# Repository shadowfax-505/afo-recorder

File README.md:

# AFO Research Recorder

An engineering research platform for synchronized lower-limb EMG and motion acquisition. The recorder samples two MyoWare 2.0 RAW channels by default, supports foot and shank IMUs, stores the primary recording on microSD, and sends a best-effort live copy over ESP32-S3 Wi-Fi.

[Open the live project](https://shadowfax-505.github.io/afo-recorder/) · [Read the documentation](https://shadowfax-505.github.io/afo-recorder/documentation/) · [Download complete packages](https://github.com/shadowfax-505/afo-recorder/releases/tag/v0.1.6)

> **Engineering status:** the firmware, file format, host tools, PCB rules, wiring data, simulations, and browser viewers have automated evidence. No recorder has yet passed the physical bench sequence. This repository does not claim measured signal quality, runtime, wearable safety, or clinical performance.

## What is included

| Layer | Included | Current evidence |
|---|---|---|
| Acquisition | ESP32-S3 firmware for AD7606 or ADS131M04 and two IMU families | Released profiles compile; hardware timing remains unmeasured |
| Storage | Versioned binary records, counters, metadata, CRC, and interrupted-file recovery | Converter and fault-injection tests pass |
| Live view | Best-effort Wi-Fi receiver for a laptop | Loopback/software checks only |
| Hardware | Breadboard plans, compact PCB projects, manufacturing exports, and 3D viewers | ERC/DRC and consistency checks pass; fabrication review remains open |
| Lab workflow | Ten gated stages from power rails to MyoWare integration | Procedures and result sheets supplied; measured results are blank |

## Choose a configuration

All packages target 8 kHz per enabled EMG channel and 200 Hz from each foot/shank IMU.

| ADC | EMG capacity | Motion sensor | Package |
|---|---:|---|---|
| AD7606, 16-bit simultaneous | Fixed 2 | ICM-42688-P | `ad7606-two-channel-icm42688` |
| AD7606, 16-bit simultaneous | Fixed 2 | GY-521 / MPU-6050 | `ad7606-two-channel-mpu6050` |
| AD7606, 16-bit simultaneous | 2 or 4 | ICM-42688-P | `ad7606-expandable-icm42688` |
| AD7606, 16-bit simultaneous | 2 or 4 | GY-521 / MPU-6050 | `ad7606-expandable-mpu6050` |
| ADS131M04, 24-bit simultaneous | 2 or 4 | ICM-42688-P | `ads131m04-expandable-icm42688` |
| ADS131M04, 24-bit simultaneous | 2 or 4 | GY-521 / MPU-6050 | `ads131m04-expandable-mpu6050` |

Use one package end to end. Do not combine an ICM wiring plan with MPU firmware or a breadboard binary with the compact-PCB SD pin assignment. The fixed-two packages intentionally reject four-channel builds.

### Arduino Mega bench setup

A separate, simpler setup lives in [`designs/mega-myoware-shield-mpu6050`](designs/mega-myoware-shield-mpu6050/README.md): an Arduino Mega 2560 with the MyoWare 2.0 Arduino Shield, up to two MPU-6050 IMUs and a ZS-040 Bluetooth module, plus a browser app for live readings and saved recordings. It uses the Mega's 10-bit ADC at up to a few hundred samples per second, so it is not a substitute for the six packages above.

## Start here

1. Read the [project manual](documentation/README.md) and choose one package.
2. Open that package's `viewer/build.html` and begin at Stage 1.
3. Qualify each module before attaching it to the controller.
4. Use synthetic signals with no person attached for every instrument-connected test.
5. Record actual measurements and pass every stage before ordering the compact PCB.

For a local copy of the website:

```sh
python3 -m http.server 8769
```

Then open <http://127.0.0.1:8769/>. The 3D viewers require HTTP and do not work correctly from a `file://` URL.

## Repository map

```text
designs/<configuration>/
├── breadboard/      terminal-level plans, placements, and wire tables
├── firmware/        ESP-IDF source and build profiles
├── hardware/        KiCad source and module references
├── host/            converter, live receiver, plots, and tests
├── manufacturing/   Gerber, drill, BOM, placement, and STEP exports
├── simulations/     analog and acquisition fault models
├── docs/            package-specific build and validation records
└── viewer/          guided build, 3D assembly, and PCB preview

documentation/       project-wide manual, status, and evidence summaries
validation/          blank or user-entered bench-session records
design-catalog.json  machine-readable list of all six configurations
```

## Validation language

The focused **AD7606 / fixed two-channel / ICM-42688-P** build has a [current integrated verification report](designs/ad7606-two-channel-icm42688/docs/integrated-verification.md). Its laboratory firmware is now **ad7606-2ch-1.12**, and **all 18 integrated Wokwi cases pass on its simulation image** (12 October 2026; the 1.11 run exposed a Wi-Fi preview race that 1.12 fixes) (32/30 µs ICM-42688 timestamp ticks, 2.44 s PSRAM record queue, per-device Wi-Fi password, IMU-only bench verdicts at the datasheet’s ±2 % clock tolerance, fitted IMU host time); its [ICM-42688-P setup](designs/ad7606-two-channel-icm42688/docs/icm-module.md) was checked against the official TDK datasheet (DS-000347 rev 1.6) and a register-level sensor model, and its AD7606 against ADI’s Rev. G data sheet. Following ADI AN-1091, the PCB now holds the ADC in shutdown until the firmware releases STBY on GPIO14, and a BAT760 diode limits VDRIVE − AVCC during power-up (DRC/ERC clean; not yet built). It compiles and passes the host and native tests but has not been rerun in Wokwi. All 18 v1.6 cases pass actual ESP-IDF execution in Wokwi’s web simulator, with real FreeRTOS/FatFS/lwIP and documented sensor, storage and radio substitutes. Nominal saved acquisition has no detected sample loss; current laptop socket/API/browser/archive checks correctly retain preview and packet gaps. Local coverage includes a 60-second, 480,000-frame production-driver pipeline. The unqualified QEMU timing experiment and historical incomplete CLI runs remain visible. Physical performance remains unmeasured; On 12 October 2026 the three other AD7606 designs received the same STBY/supply-ramp PCB fix and firmware (dual-1.4 / mpu6050-1.4); the ADS131M04 designs need none. On 12 October 2026 the other five designs also received the 1.12 Wi-Fi preview fix (each live session's metadata is sent before its first data packet) and were rebuilt as dual-1.5 / mpu6050-1.5; they were not rerun in Wokwi. On 11 October 2026 the other five designs received the shared firmware fixes (PSRAM record queue, per-device Wi-Fi password, metadata limit; 32/30 µs ticks for the ICM designs) and the fixed-two recorder corrections (worker lifecycle, fault latching, AD7606 BUSY confirmation, windowed diagnostics) and were rebuilt (firmware dual-1.3 / mpu6050-1.3); their other evidence is unchanged.

- **Verified in software** means a check, build, simulation, or test has a saved result in this repository.
- **Simulated** means generated inputs exercised a model or data path; it is not a hardware measurement.
- **Pending hardware** means the result must be measured on the assembled module, breadboard, or PCB.
- **Passed — measured** should be entered only by the person who performed the lab procedure and retained the evidence.

The latest project-level evidence reports six host suites with 242 tests, 26 compiled recording profiles, clean ERC/DRC reports for all six variants, and complete named wiring inventories. The same evidence explicitly marks physical validation as pending.

## Safety and research use

Disconnect charging cables, USB, and mains-connected instruments while electrodes are attached. Early electrical tests use synthetic sources with no person attached. Human recordings require appropriate institutional approval, informed consent, and an electrical-safety review. This system is a research recorder, not a medical device or an AFO controller.

## Documentation and attribution

- [Project manual and reading order](documentation/README.md)
- [System architecture](documentation/system-architecture.md)
- [Staged lab build](documentation/lab-build-guide.md)
- [Recording and analysis](documentation/recording-and-analysis.md)
- [Validation status](documentation/validation-status.md)
- [Manufacturer evidence](documentation/manufacturer-evidence.md)
- [Third-party notices](THIRD_PARTY_NOTICES.md)

Project lead: **Muttakin Rahman**. Manufacturer credits, source references, and third-party licence notices are retained. Publication does not change the ownership of external boards, CAD, datasheets, libraries, or photographs.

Open the [complete-system guide](designs/ad7606-two-channel-icm42688/docs/whole-system.md) for the physical assembly, saved Wokwi scene and downloadable simulation bundle.

The latest focused checks include a [complete-scene digital timing capture](designs/ad7606-two-channel-icm42688/docs/digital-timing.md) and a [saved-data interpretation guide](designs/ad7606-two-channel-icm42688/docs/data-interpretation.md). The independent audit checks 21,116 original record CRCs and CSV rows across two synthetic captures. Downloadable examples include binary recordings, metadata, quality reports and readable analysis tables; original measurement bytes are preserved. Physical storage, signal accuracy and timing calibration remain pending.

## Active build: sequential development

The [AD7606 two-channel / ICM-42688-P workbook](designs/ad7606-two-channel-icm42688/development/README.md) organizes assembly, exact new wires, measurements and evidence review one module at a time. Read the [personal system explanation](designs/ad7606-two-channel-icm42688/docs/understanding-the-recorder.md) for the AFO and neuromuscular research rationale. The other five configurations remain unchanged.

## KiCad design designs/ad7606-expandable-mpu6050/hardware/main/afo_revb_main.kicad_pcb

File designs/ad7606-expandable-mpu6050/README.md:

# Project lead: Muttakin Rahman

Start with [the guided build](viewer/build.html). The [source and licence notices](THIRD_PARTY_NOTICES.md) distinguish project material from third-party assets.

> Current assembly entrypoint: [complete build guide](docs/build-guide.html), [module qualification](docs/module-qualification.md), and [current validation](docs/validation-report.md). Historical reports and stage overview drawings are retained for traceability.

# AD7606 · Two or four EMG channels — MPU-6050

**12 October 2026 firmware update (`mpu6050-1.5`):** the Wi-Fi live task now announces a new session (its metadata packet) before that session's first data packet. Earlier firmware could send a record dequeued just after the per-loop metadata check first, and the laptop receiver dropped it as an unknown session. `firmware/main/wifi_live.c` is now byte-identical to the fixed two-channel AD7606 / ICM design's `ad7606-2ch-1.12`, where the fix was found by and passes the 18-case Wokwi matrix; this package was not rerun in Wokwi. All profiles were rebuilt with ESP-IDF v5.4.2 and host tests pass; cross-compiled only, not flashed or simulated.

**12 October 2026 PCB and firmware update (`mpu6050-1.4`):** the AD7606 supply rail is made from 3V3D by a charge pump, so VDRIVE rises before AVCC at every power-up. Following ADI application note AN-1091, AD7606 STBY (pin 7) is now driven by ESP32 GPIO14 with a 100 kΩ pull-down (R70), so the converter stays in full shutdown until the firmware releases it, waits 30 ms and resets it. A BAT760 Schottky (D30) from 3V3D to 5V_ADC limits VDRIVE − AVCC while the pump starts. The pin-8 (RANGE) ground tie that blocked pin 7 was re-routed to its own ground via. KiCad DRC (0 violations, 0 unconnected) and ERC (0) are clean, the package validator passes, and manufacturing files were re-exported; the board has not been built. Breadboard builds do not drive GPIO14. The same change, with its datasheet analysis, is described in the fixed two-channel ICM design's [circuit review](../ad7606-two-channel-icm42688/docs/circuit-audit.html).

**11 October 2026 firmware update (`mpu6050-1.3`):** the SD record queue now holds 20,480 records (about 2.44 s) in PSRAM instead of 2,048 (0.244 s), which was shorter than the 250–500 ms write-busy time an SD card may legally take; no Wi-Fi password is compiled in: each recorder generates a random 16-character password on first boot, stores it in NVS and prints it on the USB console at every boot (`Laptop AP: AFO-Recorder-B; password: …`); read it once at the bench and keep it private; the live-metadata limit is 1,800 bytes: this package's session metadata (about 1,360–1,430 bytes) exceeded the previous 1,280-byte limit, so earlier firmware silently disabled the Wi-Fi preview. All profiles were rebuilt with ESP-IDF v5.4.2 and are cross-compiled only, not flashed or simulated. Firmware `mpu6050-1.3` (same day) also ports the corrections from the fixed-two AD7606/ICM recorder: the AD7606 driver confirms BUSY after every CONVST, waits for BUSY to fall within an 80 µs deadline, and stops rather than reading a stale or overlapping conversion; recording tasks are suspended and then joined and deleted by the recorder, so an early fault cannot free a task the recorder still uses; any fault stops acquisition; both IMU stop calls are attempted; queued data is synced before the END record, and the Wi-Fi stop verdict is sent only after the final write, sync and close checks; diagnostics acquire in one-second windows and stop triggers while printing; the IMU waits up to 100 ms for its first interrupt. The fixed-two native recorder harness (19 fault and lifecycle cases) passes for every profile of this package under ASan/UBSan.

[Open the assembly viewer](viewer/index.html) · [Build guide](docs/staged-build-guide.md) · [Wiring guide](docs/breadboard-assembly.md)

[MPU wiring, timing and limits](docs/mpu6050-wiring-and-timing.md) · [Validation report](docs/validation-report.md)

Serve this folder over HTTP; opening the viewer directly as a local HTML file will block asset fetches in most browsers. Standard filenames such as CMakeLists.txt, main.c, index.html and KiCad project members are retained for tool compatibility.

All hardware remains an engineering prototype pending physical validation. Module pin positions and outstanding wiring gates are documented; no board order is implied.

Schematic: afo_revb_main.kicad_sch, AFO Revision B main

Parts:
C1, C10, C32, C33, C34, C43, C44, C200, C201, C202, C204: 100nF; C_0603_1608Metric; MPN GRM188R71C104KA01D
C2, C203, C207, C208: 10uF; C_0805_2012Metric; MPN GRM21BR61A106KE19L
C3, C30, C31, C45, C46, C205, C206, C212: 1uF; C_0603_1608Metric; MPN GRM188R61A105KA61D
C11, C40, C41, C42: 22uF; C_0805_2012Metric; MPN GRM21BR61A226ME44L
C12: 10nF; C_0603_1608Metric; MPN GRM188R71H103KA01D
C100, C101, C110, C111, C120, C121, C130, C131: 47nF; C_0603_1608Metric; MPN GRM188R71H473KA61D
C102, C112, C122, C132: 1nF; C_0603_1608Metric; MPN GRM1885C1H102JA01D
C210, C211: 2.2uF; C_0603_1608Metric; MPN GRM188R61A225KE15D
D1: USB ESD; SOT-23-6; MPN USBLC6-2SC6
D10, D11, D12, D13: BAV199; SOT-23; MPN BAV199,215
D20: green; LED_0603_1608Metric; MPN LTST-C190KGKT
D21: red; LED_0603_1608Metric; MPN LTST-C190KRKT
D22: amber; LED_0603_1608Metric; MPN LTST-C190KSKT
D30: BAT760; D_SOD-323; MPN BAT760,115
H1, H2, H3: M2 mounting; MountingHole_2.2mm_M2; MPN MECHANICAL
J1: USB-C (battery powered); USB_C_Receptacle_GCT_USB4105-xx-A_16P_TopMnt_Horizontal; MPN USB4105-GF-A
J2: microSD; microSD_HC_Hirose_DM3AT-SF-PEJM5; MPN DM3AT-SF-PEJM5
J3: FOOT MPU6050; JST_GH_BM08B-GHS-TBT_1x08-1MP_P1.25mm_Vertical; MPN BM08B-GHS-TBT(LF)(SN)
J4: SHANK MPU6050; JST_GH_BM08B-GHS-TBT_1x08-1MP_P1.25mm_Vertical; MPN BM08B-GHS-TBT(LF)(SN)
J5: EMG1; JST_GH_BM03B-GHS-TBT_1x03-1MP_P1.25mm_Vertical; MPN BM03B-GHS-TBT(LF)(SN)
J6: EMG2; JST_GH_BM03B-GHS-TBT_1x03-1MP_P1.25mm_Vertical; MPN BM03B-GHS-TBT(LF)(SN)
J7: EMG3; JST_GH_BM03B-GHS-TBT_1x03-1MP_P1.25mm_Vertical; MPN BM03B-GHS-TBT(LF)(SN)
J8: EMG4; JST_GH_BM03B-GHS-TBT_1x03-1MP_P1.25mm_Vertical; MPN BM03B-GHS-TBT(LF)(SN)
J9: PROTECTED 1S BATTERY; JST_GH_BM02B-GHS-TBT_1x02-1MP_P1.25mm_Vertical; MPN BM02B-GHS-TBT(LF)(SN)
J10: Expansion; JST_GH_BM06B-GHS-TBT_1x06-1MP_P1.25mm_Vertical; MPN BM06B-GHS-TBT(LF)(SN)
L1: 1.5uH; L_Coilcraft_XAL4020-XXX; MPN XAL4020-152MEC
Q1: DMP2035U; SOT-23; MPN DMP2035U-7
Q2: 2N7002; SOT-23; MPN 2N7002,215
R1, R2, R3, R10, R11, R12, R13, R14, R26, R30, R31, R33, R40, R41: 10k; R_0603_1608Metric; MPN RC0603FR-0710KL
R15, R22, R23: 33; R_0603_1608Metric; MPN RC0603FR-0733RL
R20, R21: 5.1k; R_0603_1608Metric; MPN RC0603FR-075K1L
R24, R51, R52, R53, R54, R70: 100k; R_0603_1608Metric; MPN RC0603FR-07100KL
R25, R101, R111, R121, R131: 1M; R_0603_1608Metric; MPN RC0603FR-071ML
R42, R104, R114, R124, R134: 100; R_0603_1608Metric; MPN RC0603FR-07100RL
R50: 316k; R_0603_1608Metric; MPN RC0603FR-07316KL
R60, R61, R62: 1k; R_0603_1608Metric; MPN RC0603FR-071KL
R100, R102, R110, R112, R120, R122, R130, R132: 3.3k; R_0603_1608Metric; MPN RC0603FR-073K3L
SW1: POWER; SW_SPDT_CK_JS102011SAQN; MPN JS102011SAQN
SW2: BOOT; SW_SPST_TL3342; MPN TL3342F160QG
SW3: EN; SW_SPST_TL3342; MPN TL3342F160QG
SW4: BUTTON; SW_SPST_TL3342; MPN TL3342F160QG
U1: ESP32-S3-WROOM-1-N8R8; ESP32-S3-WROOM-1; MPN ESP32-S3-WROOM-1-N8R8
U2: AD7606BSTZ; LQFP-64_10x10mm_P0.5mm; MPN AD7606BSTZ
U3, U4: MCP6004T-I/ST; TSSOP-14_4.4x5mm_P0.65mm; MPN MCP6004T-I/ST
U5: MCP6001T-I/OT; SOT-23-5; MPN MCP6001T-I/OT
U6: TPS63070RNMR; TI_RNM0015A; MPN TPS63070RNMR
U7: TPS7A2030PDBVR; SOT-23-5; MPN TPS7A2030PDBVR
U8: TPS60150DRVR; TPS60150_DRV0006D; MPN TPS60150DRVR

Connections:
3V0A: C32.1 (3V0A), C33.1 (3V0A), C34.1 (3V0A), C46.1 (3V0A), D10.2 (3V0A), D11.2 (3V0A), D12.2 (3V0A), D13.2 (3V0A), J5.1 (3V0A), J6.1 (3V0A), J7.1 (3V0A), J8.1 (3V0A), R40.1 (3V0A), U3.4 (3V0A), U4.4 (3V0A), U5.5 (3V0A), U7.5 (3V0A)
3V3D: C1.1 (3V3D), C2.1 (3V3D), C10.1 (3V3D), C11.1 (3V3D), C41.1 (3V3D), C42.1 (3V3D), C45.1 (3V3D), C204.1 (3V3D), C210.1 (3V3D), D30.2 (A), J2.4 (3V3D), J3.1 (3V3D), J4.1 (3V3D), J10.1 (3V3D), R1.1 (3V3D), R2.1 (3V3D), R3.1 (3V3D), R10.1 (3V3D), R11.1 (3V3D), R12.1 (3V3D), R13.1 (3V3D), R14.1 (3V3D), R26.1 (3V3D), R30.1 (3V3D), R31.1 (3V3D), R33.1 (3V3D), R50.1 (3V3D), R52.1 (3V3D), U1.2 (3V3), U2.6 (PAR_SER), U2.23 (VDRIVE), U2.34 (REF_SELECT), U6.7 (3V3D), U6.8 (3V3D), U7.1 (3V3D), U7.3 (3V3D), U8.2 (3V3D), U8.6 (3V3D)
5V_ADC: C200.1 (5V_ADC), C201.1 (5V_ADC), C202.1 (5V_ADC), C203.1 (5V_ADC), C211.1 (5V_ADC), D30.1 (K), U2.1 (AVCC), U2.37 (5V_ADC), U2.38 (5V_ADC), U2.48 (5V_ADC), U8.3 (5V_ADC)
ADC_CONVST: U1.19 (GPIO11), U2.9 (CONVST_A), U2.10 (CONVST_B)
ADC_CS: R33.2 (ADC_CS), U1.18 (GPIO10), U2.13 (CS_N)
ADC_DRDY: U1.12 (GPIO8), U2.14 (BUSY)
ADC_MISO: U1.21 (GPIO13), U2.24 (DOUTA)
ADC_REF: C207.1 (ADC_REF), U2.42 (REFIN_OUT)
ADC_REFCAP: C208.1 (ADC_REFCAP), U2.44 (REFCAP_A), U2.45 (REFCAP_B)
ADC_RESET: U1.17 (GPIO9), U2.11 (RESET)
ADC_SCK: U1.20 (GPIO12), U2.12 (SCLK)
ADC_STBY: R70.1 (ADC_STBY), U1.22 (GPIO14), U2.7 (STBY_N)
AIN0P: C102.1 (AIN0P), R104.2 (AIN0P), U2.49 (AIN0P)
AIN1P: C112.1 (AIN1P), R114.2 (AIN1P), U2.51 (AIN1P)
AIN2P: C122.1 (AIN2P), R124.2 (AIN2P), U2.53 (AIN2P)
AIN3P: C132.1 (AIN3P), R134.2 (AIN3P), U2.55 (AIN3P)
BAT_SENSE: C44.1 (BAT_SENSE), R53.2 (BAT_SENSE), R54.1 (BAT_SENSE), U1.39 (GPIO1)
BOOT: R2.2 (BOOT), SW2.1 (BOOT), U1.27 (GPIO0)
BUF0A: R102.1 (BUF0A), U3.1 (BUF0A), U3.2 (BUF0A)
BUF0B: R104.1 (BUF0B), U4.1 (BUF0B), U4.2 (BUF0B)
BUF1A: R112.1 (BUF1A), U3.6 (BUF1A), U3.7 (BUF1A)
BUF1B: R114.1 (BUF1B), U4.6 (BUF1B), U4.7 (BUF1B)
BUF2A: R122.1 (BUF2A), U3.8 (BUF2A), U3.9 (BUF2A)
BUF2B: R124.1 (BUF2B), U4.8 (BUF2B), U4.9 (BUF2B)
BUF3A: R132.1 (BUF3A), U3.13 (BUF3A), U3.14 (BUF3A)
BUF3B: R134.1 (BUF3B), U4.13 (BUF3B), U4.14 (BUF3B)
BUTTON: R3.2 (BUTTON), SW4.1 (BUTTON), U1.11 (GPIO18)
CP_MINUS: C212.2 (CP_MINUS), U8.5 (CP_MINUS)
CP_PLUS: C212.1 (CP_PLUS), U8.4 (CP_PLUS)
EN: C3.1 (EN), R1.2 (EN), SW3.1 (EN), U1.3 (EN)
EXP_SCL: J10.4 (EXP_SCL), U1.25 (GPIO48)
EXP_SDA: J10.3 (EXP_SDA), U1.24 (GPIO47)
FB: R50.2 (FB), R51.1 (FB), U6.5 (FB)
FOOT_AD0: J3.6 (FOOT_AD0), R30.2 (FOOT_AD0), U1.7 (GPIO7)
FOOT_INT: J3.7 (FOOT_INT), U1.9 (GPIO16)
GND: C1.2 (GND), C2.2 (GND), C3.2 (GND), C10.2 (GND), C11.2 (GND), C12.2 (GND), C30.2 (GND), C31.2 (GND), C32.2 (GND), C33.2 (GND), C34.2 (GND), C40.2 (GND), C41.2 (GND), C42.2 (GND), C43.2 (GND), C44.2 (GND), C45.2 (GND), C46.2 (GND), C100.2 (GND), C101.2 (GND), C102.2 (GND), C110.2 (GND), C111.2 (GND), C112.2 (GND), C120.2 (GND), C121.2 (GND), C122.2 (GND), C130.2 (GND), C131.2 (GND), C132.2 (GND), C200.2 (GND), C201.2 (GND), C202.2 (GND), C203.2 (GND), C204.2 (GND), C205.2 (GND), C206.2 (GND), C207.2 (GND), C208.2 (GND), C210.2 (GND), C211.2 (GND), D1.2 (GND), D10.1 (GND), D11.1 (GND), D12.1 (GND), D13.1 (GND), D20.1 (GND), D21.1 (GND), D22.1 (GND), J1.A1 (GND), J1.A12 (GND), J1.B1 (GND), J1.B12 (GND), J1.SH (GND), J2.6 (GND), J2.SH (GND), J3.2 (GND), J3.8 (GND), J4.2 (GND), J4.8 (GND), J5.2 (GND), J6.2 (GND), J7.2 (GND), J8.2 (GND), J9.2 (GND), J10.2 (GND), Q1.1 (GND), Q2.2 (GND), R20.2 (GND), R21.2 (GND), R25.2 (GND), R41.2 (GND), R51.2 (GND), R54.2 (GND), R70.2 (GND), SW1.3 (GND), SW2.2 (GND), SW3.2 (GND), SW4.2 (GND), U1.1 (GND), U1.40 (GND), U1.41 (EP_GND), U2.2 (GND), U2.3 (GND), U2.4 (GND), U2.5 (GND), U2.8 (RANGE), U2.16 (GND), U2.17 (GND), U2.18 (GND), U2.19 (GND), U2.20 (GND), U2.21 (GND), U2.22 (GND), U2.26 (GND), U2.27 (GND), U2.28 (GND), U2.29 (GND), U2.30 (GND), U2.31 (GND), U2.32 (GND), U2.33 (GND), U2.35 (GND), U2.40 (GND), U2.41 (GND), U2.43 (GND), U2.46 (GND), U2.47 (GND), U2.50 (GND), U2.52 (GND), U2.54 (GND), U2.56 (GND), U2.57 (GND), U2.58 (GND), U2.59 (GND), U2.60 (GND), U2.61 (GND), U2.62 (GND), U2.63 (GND), U2.64 (GND), U3.11 (GND), U4.11 (GND), U5.2 (GND), U6.1 (GND), U6.4 (GND), U6.6 (GND), U6.10 (GND), U6.15 (GND), U7.2 (GND), U8.1 (GND), U8.7 (GND)
IMU_RESERVED: J3.5 (IMU_RESERVED), J4.5 (IMU_RESERVED), U1.5 (GPIO5)
IMU_SCL: J3.3 (IMU_SCL), J4.3 (IMU_SCL), U1.6 (GPIO6)
IMU_SDA: J3.4 (IMU_SDA), J4.4 (IMU_SDA), U1.4 (GPIO4)
LED_ERR: R61.1 (LED_ERR), U1.35 (GPIO42)
LED_ERR_A: D21.2 (LED_ERR_A), R61.2 (LED_ERR_A)
LED_LOW: R62.1 (LED_LOW), U1.38 (GPIO2)
LED_LOW_A: D22.2 (LED_LOW_A), R62.2 (LED_LOW_A)
LED_REC: R60.1 (LED_REC), U1.34 (GPIO41)
LED_REC_A: D20.2 (LED_REC_A), R60.2 (LED_REC_A)
PACK_PLUS: J9.1 (PACK_PLUS), Q1.3 (PACK_PLUS)
POWER_EN: SW1.2 (POWER_EN), U6.14 (POWER_EN)
POWER_GOOD: R52.2 (POWER_GOOD), U6.2 (POWER_GOOD)
RAW0: J5.3 (RAW0), R100.1 (RAW0), R101.1 (RAW0)
RAW1: J6.3 (RAW1), R110.1 (RAW1), R111.1 (RAW1)
RAW2: J7.3 (RAW2), R120.1 (RAW2), R121.1 (RAW2)
RAW3: J8.3 (RAW3), R130.1 (RAW3), R131.1 (RAW3)
RC0A: C100.1 (RC0A), D10.3 (RC0A), R100.2 (RC0A), U3.3 (RC0A)
RC0B: C101.1 (RC0B), R102.2 (RC0B), U4.3 (RC0B)
RC1A: C110.1 (RC1A), D11.3 (RC1A), R110.2 (RC1A), U3.5 (RC1A)
RC1B: C111.1 (RC1B), R112.2 (RC1B), U4.5 (RC1B)
RC2A: C120.1 (RC2A), D12.3 (RC2A), R120.2 (RC2A), U3.10 (RC2A)
RC2B: C121.1 (RC2B), R122.2 (RC2B), U4.10 (RC2B)
RC3A: C130.1 (RC3A), D13.3 (RC3A), R130.2 (RC3A), U3.12 (RC3A)
RC3B: C131.1 (RC3B), R132.2 (RC3B), U4.12 (RC3B)
REGCAP_A: C205.1 (REGCAP_A), U2.36 (REGCAP_A)
REGCAP_B: C206.1 (REGCAP_B), U2.39 (REGCAP_B)
SD_CLK: J2.5 (SD_CLK), R15.2 (SD_CLK)
SD_CLK_MCU: R15.1 (SD_CLK_MCU), U1.32 (GPIO39)
SD_CMD: J2.3 (SD_CMD), R10.2 (SD_CMD), U1.31 (GPIO38)
SD_D0: J2.7 (SD_D0), R11.2 (SD_D0), U1.33 (GPIO40)
SD_D1: J2.8 (SD_D1), R12.2 (SD_D1)
SD_D2: J2.1 (SD_D2), R13.2 (SD_D2)
SD_D3: J2.2 (SD_D3), R14.2 (SD_D3)
SHANK_AD0: J4.6 (SHANK_AD0), R31.2 (SHANK_AD0), U1.8 (GPIO15)
SHANK_INT: J4.7 (SHANK_INT), U1.10 (GPIO17)
SW_L1: L1.1 (SW_L1), U6.11 (SW_L1)
SW_L2: L1.2 (SW_L2), U6.9 (SW_L2)
UART_RX: J10.6 (UART_RX), U1.36 (GPIO44)
UART_TX: J10.5 (UART_TX), U1.37 (GPIO43)
USB_CC1: J1.A5 (USB_CC1), R20.1 (USB_CC1)
USB_CC2: J1.B5 (USB_CC2), R21.1 (USB_CC2)
USB_DM: D1.3 (USB_DM), J1.A7 (USB_DM), J1.B7 (USB_DM), R23.1 (USB_DM)
USB_DM_MCU: R23.2 (USB_DM_MCU), U1.13 (GPIO19)
USB_DP: D1.1 (USB_DP), J1.A6 (USB_DP), J1.B6 (USB_DP), R22.1 (USB_DP)
USB_DP_MCU: R22.2 (USB_DP_MCU), U1.14 (GPIO20)
USB_GATE: C12.1 (USB_GATE), Q2.1 (USB_GATE), R24.2 (USB_GATE), R25.1 (USB_GATE)
USB_PRESENT_N: Q2.3 (USB_PRESENT_N), R26.2 (USB_PRESENT_N), U1.23 (GPIO21)
USB_VBUS: D1.5 (USB_VBUS), J1.A4 (USB_VBUS), J1.A9 (USB_VBUS), J1.B4 (USB_VBUS), J1.B9 (USB_VBUS), R24.1 (USB_VBUS)
VAUX: C43.1 (VAUX), U6.3 (VAUX)
VBAT: C40.1 (VBAT), Q1.2 (VBAT), R53.1 (VBAT), SW1.1 (VBAT), U6.12 (VBAT), U6.13 (VBAT)
VMID: C31.1 (VMID), R42.2 (VMID), R101.2 (VMID), R111.2 (VMID), R121.2 (VMID), R131.2 (VMID)
VMID_BUF: R42.1 (VMID_BUF), U5.1 (VMID_BUF), U5.4 (VMID_BUF)
VMID_DIV: C30.1 (VMID_DIV), R40.2 (VMID_DIV), R41.1 (VMID_DIV), U5.3 (VMID_DIV)

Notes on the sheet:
DIGITAL
ADC
ANALOG
POWER
MECHANICAL

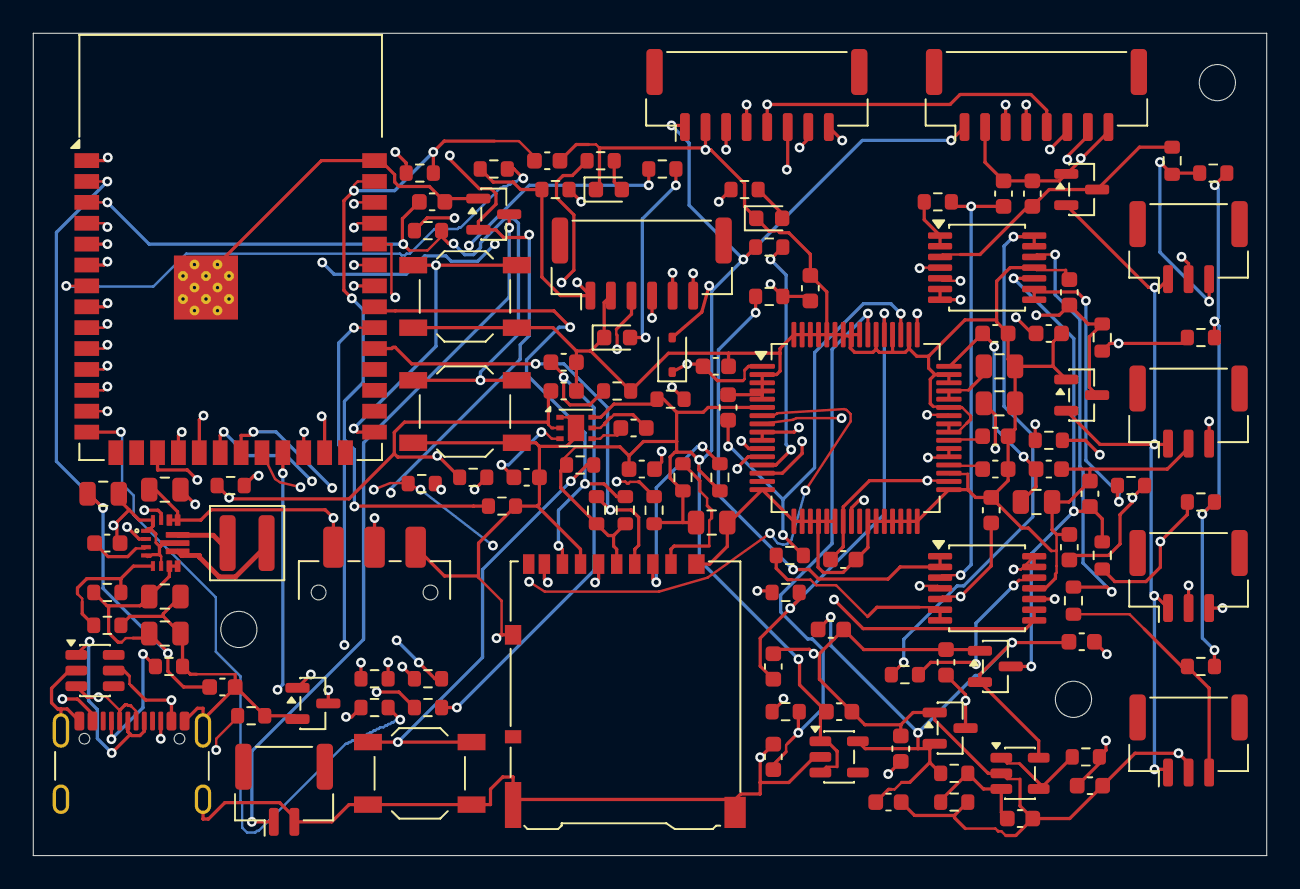
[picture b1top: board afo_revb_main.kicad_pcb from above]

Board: 4 copper layers, 75.0 x 50.0 mm, 126 parts (0 on the bottom side), 89 nets.

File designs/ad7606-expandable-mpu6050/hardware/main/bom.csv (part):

Reference,Value,Manufacturer part number,Footprint,Populate
U1,ESP32-S3-WROOM-1-N8R8,ESP32-S3-WROOM-1-N8R8,RF_Module:ESP32-S3-WROOM-1,Yes
C1,100nF,GRM188R71C104KA01D,Capacitor_SMD:C_0603_1608Metric,Yes
C2,10uF,GRM21BR61A106KE19L,Capacitor_SMD:C_0805_2012Metric,Yes
R1,10k,RC0603FR-0710KL,Resistor_SMD:R_0603_1608Metric,Yes
C3,1uF,GRM188R61A105KA61D,Capacitor_SMD:C_0603_1608Metric,Yes
R2,10k,RC0603FR-0710KL,Resistor_SMD:R_0603_1608Metric,Yes
R3,10k,RC0603FR-0710KL,Resistor_SMD:R_0603_1608Metric,Yes
SW2,BOOT,TL3342F160QG,Button_Switch_SMD:SW_SPST_TL3342,Yes
SW3,EN,TL3342F160QG,Button_Switch_SMD:SW_SPST_TL3342,Yes
SW4,BUTTON,TL3342F160QG,Button_Switch_SMD:SW_SPST_TL3342,Yes
J2,microSD,DM3AT-SF-PEJM5,Connector_Card:microSD_HC_Hirose_DM3AT-SF-PEJM5,Yes
R10,10k,RC0603FR-0710KL,Resistor_SMD:R_0603_1608Metric,Yes
R11,10k,RC0603FR-0710KL,Resistor_SMD:R_0603_1608Metric,Yes
R12,10k,RC0603FR-0710KL,Resistor_SMD:R_0603_1608Metric,Yes
R13,10k,RC0603FR-0710KL,Resistor_SMD:R_0603_1608Metric,Yes
R14,10k,RC0603FR-0710KL,Resistor_SMD:R_0603_1608Metric,Yes
R15,33,RC0603FR-0733RL,Resistor_SMD:R_0603_1608Metric,Yes
C10,100nF,GRM188R71C104KA01D,Capacitor_SMD:C_0603_1608Metric,Yes
C11,22uF,GRM21BR61A226ME44L,Capacitor_SMD:C_0805_2012Metric,Yes
J1,USB-C (battery powered),USB4105-GF-A,Connector_USB:USB_C_Receptacle_GCT_USB4105-xx-A_16P_TopMnt_Horizontal,Yes
R20,5.1k,RC0603FR-075K1L,Resistor_SMD:R_0603_1608Metric,Yes
R21,5.1k,RC0603FR-075K1L,Resistor_SMD:R_0603_1608Metric,Yes
R22,33,RC0603FR-0733RL,Resistor_SMD:R_0603_1608Metric,Yes
R23,33,RC0603FR-0733RL,Resistor_SMD:R_0603_1608Metric,Yes
R24,100k,RC0603FR-07100KL,Resistor_SMD:R_0603_1608Metric,Yes
R25,1M,RC0603FR-071ML,Resistor_SMD:R_0603_1608Metric,Yes
R26,10k,RC0603FR-0710KL,Resistor_SMD:R_0603_1608Metric,Yes
Q2,2N7002,"2N7002,215",Package_TO_SOT_SMD:SOT-23,Yes
C12,10nF,GRM188R71H103KA01D,Capacitor_SMD:C_0603_1608Metric,Yes
D1,USB ESD,USBLC6-2SC6,Package_TO_SOT_SMD:SOT-23-6,Yes
J3,FOOT MPU6050,BM08B-GHS-TBT(LF)(SN),Connector_JST:JST_GH_BM08B-GHS-TBT_1x08-1MP_P1.25mm_Vertical,Yes
J4,SHANK MPU6050,BM08B-GHS-TBT(LF)(SN),Connector_JST:JST_GH_BM08B-GHS-TBT_1x08-1MP_P1.25mm_Vertical,Yes
R30,10k,RC0603FR-0710KL,Resistor_SMD:R_0603_1608Metric,Yes
R31,10k,RC0603FR-0710KL,Resistor_SMD:R_0603_1608Metric,Yes
U2,AD7606BSTZ,AD7606BSTZ,Package_QFP:LQFP-64_10x10mm_P0.5mm,Yes
R33,10k,RC0603FR-0710KL,Resistor_SMD:R_0603_1608Metric,Yes
R40,10k,RC0603FR-0710KL,Resistor_SMD:R_0603_1608Metric,Yes
R41,10k,RC0603FR-0710KL,Resistor_SMD:R_0603_1608Metric,Yes
C30,1uF,GRM188R61A105KA61D,Capacitor_SMD:C_0603_1608Metric,Yes
U5,MCP6001T-I/OT,MCP6001T-I/OT,Package_TO_SOT_SMD:SOT-23-5,Yes
R42,100,RC0603FR-07100RL,Resistor_SMD:R_0603_1608Metric,Yes
C31,1uF,GRM188R61A105KA61D,Capacitor_SMD:C_0603_1608Metric,Yes
C32,100nF,GRM188R71C104KA01D,Capacitor_SMD:C_0603_1608Metric,Yes
U3,MCP6004T-I/ST,MCP6004T-I/ST,Package_SO:TSSOP-14_4.4x5mm_P0.65mm,Yes
U4,MCP6004T-I/ST,MCP6004T-I/ST,Package_SO:TSSOP-14_4.4x5mm_P0.65mm,Yes
C33,100nF,GRM188R71C104KA01D,Capacitor_SMD:C_0603_1608Metric,Yes
C34,100nF,GRM188R71C104KA01D,Capacitor_SMD:C_0603_1608Metric,Yes
J5,EMG1,BM03B-GHS-TBT(LF)(SN),Connector_JST:JST_GH_BM03B-GHS-TBT_1x03-1MP_P1.25mm_Vertical,Yes
R100,3.3k,RC0603FR-073K3L,Resistor_SMD:R_0603_1608Metric,Yes
R101,1M,RC0603FR-071ML,Resistor_SMD:R_0603_1608Metric,Yes
C100,47nF,GRM188R71H473KA61D,Capacitor_SMD:C_0603_1608Metric,Yes
D10,BAV199,"BAV199,215",Package_TO_SOT_SMD:SOT-23,Yes
R102,3.3k,RC0603FR-073K3L,Resistor_SMD:R_0603_1608Metric,Yes
C101,47nF,GRM188R71H473KA61D,Capacitor_SMD:C_0603_1608Metric,Yes
R104,100,RC0603FR-07100RL,Resistor_SMD:R_0603_1608Metric,Yes
C102,1nF,GRM1885C1H102JA01D,Capacitor_SMD:C_0603_1608Metric,Yes
J6,EMG2,BM03B-GHS-TBT(LF)(SN),Connector_JST:JST_GH_BM03B-GHS-TBT_1x03-1MP_P1.25mm_Vertical,Yes
R110,3.3k,RC0603FR-073K3L,Resistor_SMD:R_0603_1608Metric,Yes
R111,1M,RC0603FR-071ML,Resistor_SMD:R_0603_1608Metric,Yes
C110,47nF,GRM188R71H473KA61D,Capacitor_SMD:C_0603_1608Metric,Yes
D11,BAV199,"BAV199,215",Package_TO_SOT_SMD:SOT-23,Yes
R112,3.3k,RC0603FR-073K3L,Resistor_SMD:R_0603_1608Metric,Yes
C111,47nF,GRM188R71H473KA61D,Capacitor_SMD:C_0603_1608Metric,Yes
R114,100,RC0603FR-07100RL,Resistor_SMD:R_0603_1608Metric,Yes
C112,1nF,GRM1885C1H102JA01D,Capacitor_SMD:C_0603_1608Metric,Yes
J7,EMG3,BM03B-GHS-TBT(LF)(SN),Connector_JST:JST_GH_BM03B-GHS-TBT_1x03-1MP_P1.25mm_Vertical,Yes
R120,3.3k,RC0603FR-073K3L,Resistor_SMD:R_0603_1608Metric,Yes
R121,1M,RC0603FR-071ML,Resistor_SMD:R_0603_1608Metric,Yes
C120,47nF,GRM188R71H473KA61D,Capacitor_SMD:C_0603_1608Metric,Yes
D12,BAV199,"BAV199,215",Package_TO_SOT_SMD:SOT-23,Yes
R122,3.3k,RC0603FR-073K3L,Resistor_SMD:R_0603_1608Metric,Yes
C121,47nF,GRM188R71H473KA61D,Capacitor_SMD:C_0603_1608Metric,Yes
R124,100,RC0603FR-07100RL,Resistor_SMD:R_0603_1608Metric,Yes
C122,1nF,GRM1885C1H102JA01D,Capacitor_SMD:C_0603_1608Metric,Yes
J8,EMG4,BM03B-GHS-TBT(LF)(SN),Connector_JST:JST_GH_BM03B-GHS-TBT_1x03-1MP_P1.25mm_Vertical,Yes
R130,3.3k,RC0603FR-073K3L,Resistor_SMD:R_0603_1608Metric,Yes
R131,1M,RC0603FR-071ML,Resistor_SMD:R_0603_1608Metric,Yes
C130,47nF,GRM188R71H473KA61D,Capacitor_SMD:C_0603_1608Metric,Yes
D13,BAV199,"BAV199,215",Package_TO_SOT_SMD:SOT-23,Yes
R132,3.3k,RC0603FR-073K3L,Resistor_SMD:R_0603_1608Metric,Yes
C131,47nF,GRM188R71H473KA61D,Capacitor_SMD:C_0603_1608Metric,Yes
R134,100,RC0603FR-07100RL,Resistor_SMD:R_0603_1608Metric,Yes
C132,1nF,GRM1885C1H102JA01D,Capacitor_SMD:C_0603_1608Metric,Yes
J9,PROTECTED 1S BATTERY,BM02B-GHS-TBT(LF)(SN),Connector_JST:JST_GH_BM02B-GHS-TBT_1x02-1MP_P1.25mm_Vertical,Yes
Q1,DMP2035U,DMP2035U-7,Package_TO_SOT_SMD:SOT-23,Yes
SW1,POWER,JS102011SAQN,Button_Switch_SMD:SW_SPDT_CK_JS102011SAQN,Yes
U6,TPS63070RNMR,TPS63070RNMR,RevB:TI_RNM0015A,Yes
L1,1.5uH,XAL4020-152MEC,Inductor_SMD:L_Coilcraft_XAL4020-XXX,Yes
C40,22uF,GRM21BR61A226ME44L,Capacitor_SMD:C_0805_2012Metric,Yes
C41,22uF,GRM21BR61A226ME44L,Capacitor_SMD:C_0805_2012Metric,Yes
C42,22uF,GRM21BR61A226ME44L,Capacitor_SMD:C_0805_2012Metric,Yes
C43,100nF,GRM188R71C104KA01D,Capacitor_SMD:C_0603_1608Metric,Yes
R50,316k,RC0603FR-07316KL,Resistor_SMD:R_0603_1608Metric,Yes
R51,100k,RC0603FR-07100KL,Resistor_SMD:R_0603_1608Metric,Yes
R52,100k,RC0603FR-07100KL,Resistor_SMD:R_0603_1608Metric,Yes
R53,100k,RC0603FR-07100KL,Resistor_SMD:R_0603_1608Metric,Yes
R54,100k,RC0603FR-07100KL,Resistor_SMD:R_0603_1608Metric,Yes
C44,100nF,GRM188R71C104KA01D,Capacitor_SMD:C_0603_1608Metric,Yes
U7,TPS7A2030PDBVR,TPS7A2030PDBVR,Package_TO_SOT_SMD:SOT-23-5,Yes
C45,1uF,GRM188R61A105KA61D,Capacitor_SMD:C_0603_1608Metric,Yes
C46,1uF,GRM188R61A105KA61D,Capacitor_SMD:C_0603_1608Metric,Yes
R60,1k,RC0603FR-071KL,Resistor_SMD:R_0603_1608Metric,Yes
D20,green,LTST-C190KGKT,LED_SMD:LED_0603_1608Metric,Yes
R61,1k,RC0603FR-071KL,Resistor_SMD:R_0603_1608Metric,Yes
D21,red,LTST-C190KRKT,LED_SMD:LED_0603_1608Metric,Yes
R62,1k,RC0603FR-071KL,Resistor_SMD:R_0603_1608Metric,Yes
D22,amber,LTST-C190KSKT,LED_SMD:LED_0603_1608Metric,Yes
J10,Expansion,BM06B-GHS-TBT(LF)(SN),Connector_JST:JST_GH_BM06B-GHS-TBT_1x06-1MP_P1.25mm_Vertical,Yes
H1,M2 mounting,MECHANICAL,MountingHole:MountingHole_2.2mm_M2,Mechanical
H2,M2 mounting,MECHANICAL,MountingHole:MountingHole_2.2mm_M2,Mechanical
H3,M2 mounting,MECHANICAL,MountingHole:MountingHole_2.2mm_M2,Mechanical
C200,100nF,GRM188R71C104KA01D,Capacitor_SMD:C_0603_1608Metric,Yes
C201,100nF,GRM188R71C104KA01D,Capacitor_SMD:C_0603_1608Metric,Yes
C202,100nF,GRM188R71C104KA01D,Capacitor_SMD:C_0603_1608Metric,Yes
C203,10uF,GRM21BR61A106KE19L,Capacitor_SMD:C_0805_2012Metric,Yes
C204,100nF,GRM188R71C104KA01D,Capacitor_SMD:C_0603_1608Metric,Yes
C205,1uF,GRM188R61A105KA61D,Capacitor_SMD:C_0603_1608Metric,Yes
C206,1uF,GRM188R61A105KA61D,Capacitor_SMD:C_0603_1608Metric,Yes
C207,10uF,GRM21BR61A106KE19L,Capacitor_SMD:C_0805_2012Metric,Yes
C208,10uF,GRM21BR61A106KE19L,Capacitor_SMD:C_0805_2012Metric,Yes
U8,TPS60150DRVR,TPS60150DRVR,RevB:TPS60150_DRV0006D,Yes
C210,2.2uF,GRM188R61A225KE15D,Capacitor_SMD:C_0603_1608Metric,Yes
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
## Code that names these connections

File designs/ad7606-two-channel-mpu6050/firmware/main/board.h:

#pragma once
#include "variant.h"
#define ADC_CONVST 11

// Revision B ESP32-S3-WROOM-1-N8R8. Onboard LEDs, active high.
#define ADC_DRDY 8
#define ADC_RESET 9
#define USB_PRESENT_PIN 21
#ifndef EMG_CHANNEL_COUNT
#define EMG_CHANNEL_COUNT 2
#endif
#if EMG_CHANNEL_COUNT != 2
#error "This hardware has exactly two EMG inputs"
#endif
#define ADS_CLOCK_REG ((EMG_CHANNEL_COUNT == 2 ? 0x0300 : 0x0f00) | 0x000a)
#define ADS_MODE_REG 0x0111
#define ADC_SCK 12
#define ADC_MISO 13
#define ADC_MOSI 11
#define ADC_CS 10
#define IMU_SCL 6
#define IMU_RESERVED 5
#define IMU_SDA 4
#define FOOT_AD0 7
#define SHANK_AD0 15
#define FOOT_INT 16
#define SHANK_INT 17
#define SD_CLK 39
#ifndef AFO_BREADBOARD
#define AFO_BREADBOARD 0
#endif
#if AFO_BREADBOARD
#define SD_CMD 47
#define AFO_SD_METADATA "\"sd_cmd_gpio\":47,\"sd_clk_gpio\":39,\"sd_d0_gpio\":40,"
#else
#define SD_CMD 38
#define AFO_SD_METADATA "\"sd_cmd_gpio\":38,\"sd_clk_gpio\":39,\"sd_d0_gpio\":40,"
#endif
#define SD_D0 40
// AD7606 STBY (pin 7). On the PCB, AVCC (5V_ADC) is generated from 3V3D, so
// VDRIVE rises first. A 100 k pull-down holds STBY low; with RANGE low that
// is full shutdown (ADI AN-1091) until the firmware releases it. The
// breadboard ADC module keeps its own STBY tie, so it has no STBY GPIO.
#if AFO_BREADBOARD
#define ADC_STBY -1
#else
#define ADC_STBY 14
#endif
#define ADC_WAKE_MS 30 // Rev. G Table 3 tWAKE-UP SHUTDOWN, internal reference (max).
#define BUTTON_PIN 18
#define LED_RECORD 41
#define LED_ERROR 42
#define LED_BATTERY 2
#define BATTERY_PIN 1  // ADC1 channel 0; 100k/100k divider from protected 1S pack.
#define EMG_HZ 8000
#define IMU_HZ 200
#ifndef IMU_COUNT
#define IMU_COUNT 2
#endif
#define ENABLE_IMUS (IMU_COUNT > 0)
#ifndef HARDWARE_VARIANT
#define HARDWARE_VARIANT "pcb"
#endif
#define ADC_REFERENCE_MV (AFO_AD7606 ? 5000 : 1200) // Nominal signed full-scale, not measured.
#define ADC_REFERENCE_MEASURED 0 // Set to 1 only after measuring and entering the rail voltage.
#define BATTERY_DIVIDER 2.0f
#define BATTERY_WARN_MV 3500
#define BATTERY_STOP_MV 3300
#define MIN_FREE_BYTES (64ULL * 1024 * 1024)
#define MAX_SESSION_US (2ULL * 60 * 60 * 1000000)
// 20,480 x 64-byte records in PSRAM: about 2.44 s at 8,000 EMG + 400 IMU records/s.
// The SD specification permits write-busy periods up to 250 ms (SDHC) or
// 500 ms (SDXC); the older 2,048-entry internal queue held only 0.244 s.
#define RECORD_QUEUE_LENGTH 20480

#define AFO_FIRMWARE_ID "mpu6050-1.5"
#define SD_MOUNT "/sdcard"

// Laptop preview uses a private access point. Change this bench password before deployment.
#ifndef ENABLE_WIFI_LIVE
#define ENABLE_WIFI_LIVE 1
#endif
#define WIFI_LIVE_SSID "AFO-Recorder-B"
// No password is compiled in: each recorder generates a random one on first boot,
// keeps it in NVS and prints it on the USB console at every boot.
#define WIFI_LIVE_PASSWORD_CHARS 16
// Largest metadata JSON sent to the laptop; host/live_protocol.py MAX_PAYLOAD
// must match. MPU-6050 session metadata is about 1,360-1,430 bytes, above the
// previous 1,280-byte limit (which disabled the live preview); the 1,832-byte
// metadata datagram is IP-fragmented on Wi-Fi and resent every second.
#define WIFI_LIVE_METADATA_MAX 1800
#define WIFI_LIVE_PORT 3333

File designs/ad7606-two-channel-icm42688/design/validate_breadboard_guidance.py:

#!/usr/bin/env python3
"""Check lab handoff pin identities, firmware hashes and blank result sheets."""
import csv
import hashlib
import html
from html.parser import HTMLParser
import json
from pathlib import Path
import re

VARIANT = Path(__file__).resolve().parent.parent


def sha256(path):
    return hashlib.sha256(path.read_bytes()).hexdigest()


def read_csv(path):
    with path.open(newline='') as stream:
        return list(csv.DictReader(stream))


class LinkReader(HTMLParser):
    def __init__(self):
        super().__init__()
        self.links = []

    def handle_starttag(self, tag, attrs):
        if tag == 'a':
            self.links += [value for key, value in attrs if key == 'href' and value]


def validate():
    wires = json.loads((VARIANT / 'breadboard/system-wiring.json').read_text())['connections']
    assert len(wires) == 184
    wire_by_id = {w['id']: w for w in wires}
    tables = [read_csv(VARIANT / 'breadboard' / name)
              for name in ['system-wiring.csv', 'exact-wire-endpoints.csv']]
    assert tables[0] == tables[1] and len(tables[0]) == len(wires)
    table_by_id = {r['Wire']: r for r in tables[0]}
    guide_html = (VARIANT / 'docs/build-guide.html').read_text()
    for wire in wires:
        row = table_by_id[wire['id']]
        assert row['Net'] == wire['net'] and row['Stage'] == str(wire['stage'])
        assert row['From'] == wire['a']['module'] + ':' + wire['a']['terminal']
        assert row['To'] == wire['b']['module'] + ':' + wire['b']['terminal']
        assert row['Instructions'] == wire['note']
        match = re.search(r'<tr><td>' + re.escape(wire['id']) +
                          r'</td>(?:<td>.*?</td>){4}<td>(.*?)</td></tr>', guide_html)
        assert match and html.unescape(match[1]) == wire['note'], wire['id']

    board = (VARIANT / 'firmware/main/board.h').read_text()
    pin_names = ['ADC_CONVST', 'ADC_DRDY', 'ADC_RESET', 'ADC_SCK', 'ADC_MISO', 'ADC_CS',
                 'IMU_MOSI', 'IMU_MISO', 'IMU_SCK', 'FOOT_CS', 'SHANK_CS',
                 'FOOT_INT', 'SHANK_INT', 'SD_CLK', 'SD_D0', 'USB_PRESENT_PIN']
    pins = {name: int(re.search(r'^#define ' + name + r' (\d+)$', board, re.M)[1])
            for name in pin_names}
    pins['SD_CMD'] = int(re.search(r'#if AFO_BREADBOARD\s+#define SD_CMD (\d+)', board)[1])
    pins['USB_PRESENT_N'] = pins.pop('USB_PRESENT_PIN')
    for net, gpio in pins.items():
        ends = [e for w in wires if w['net'] == net for e in [w['a'], w['b']]
                if e['module'] == 'esp']
        assert len(ends) == 1 and int(re.search(r'GPIO(\d+)', ends[0]['terminal'])[1]) == gpio, (net, gpio, ends)

    # Independently require both conversion groups on the same five-hole strip.
    trigger = [w for w in wires if w['net'] == 'ADC_CONVST']
    assert len(trigger) == 3
    assert {e['terminal'].split(' /')[0] for w in trigger for e in [w['a'], w['b']]
            if e['module'] == 'adc'} == {'CVA', 'CVB'}
    strips = [e for w in trigger for e in [w['a'], w['b']] if e['module'] == 'DIST1']
    assert {e['hole'] for e in strips} == {'a29', 'b29', 'c29'}
    assert wire_by_id['wire-111']['b']['terminal'].startswith('DB7 /')
    assert wire_by_id['wire-113']['b']['terminal'].startswith('BUSY /')

    probes = read_csv(VARIANT / 'breadboard/probe-connections.csv')
    assert len(probes) == 18
    for probe in probes:
        assert all(probe[key] == table_by_id[probe['Wire']][key]
                   for key in ['Wire', 'Stage', 'Net', 'From', 'To']), probe
        assert probe['Probe_at'] in [probe['From'], probe['To']]
    assert {'ADC_CONVST', 'ADC_DRDY', 'ADC_CS', 'ADC_SCK', 'ADC_MISO', 'ADC_RESET',
            'FOOT_INT', 'SHANK_INT', 'SD_CMD', 'SD_CLK', 'SD_D0', 'USB_PRESENT_N'} <= {p['Net'] for p in probes}

    validation = json.loads((VARIANT / 'firmware/builds/validation.json').read_text())
    assert validation['source_set'] == 'ad7606-2ch-1.12'
    for path, expected in validation['source_sha256'].items():
        assert sha256(VARIANT / 'firmware' / path) == expected, path
    assert len(validation['profiles']) == 9
    profiles = {p['profile']: p for p in validation['profiles']}
    for name, profile in profiles.items():
        assert profile['active_channels'] == 2
        for path, expected in profile['sha256'].items():
            assert sha256(VARIANT / 'firmware/builds' / name / path) == expected, (name, path)

    checks = read_csv(VARIANT / 'docs/bench-checklist.csv')
    assert len(checks) == 30 and {int(c['Stage']) for c in checks} == set(range(1, 11))
    measurement_fields = ['Firmware_application_sha256', 'Module_serial_or_photo', 'Date_operator',
                          'Instrument_calibration', 'Measured_values', 'Evidence_files', 'Reviewer']
    for check in checks:
        assert check['Outcome'] == 'NOT TESTED'
        assert all(not check[name] for name in measurement_fields), check['Check']
        if check['Firmware_profile']:
            assert profiles[check['Firmware_profile']]['hardware'] == 'breadboard', check
    guide = json.loads((VARIANT / 'viewer/guide.json').read_text())
    assert len(guide['stages']) == 10
    assert guide['stages'][4]['title'] == 'Second EMG channel'
    assert '8 kHz ±0.1%' in guide['stages'][2]['acceptance']
    assert 'GPIO47' in '\n'.join(guide['stages'][6]['tests'])

    link_count = 0
    for filename in ['breadboard-refinements.html', 'lab-quickstart.html',
                     'staged-build-guide.html', 'physical-assembly.html', 'firmware-build-guide.html',
                     'laptop-setup.html', 'download-checks.html']:
        page = VARIANT / 'docs' / filename
        links = LinkReader()
        links.feed(page.read_text())
        for link in links.links:
            if link.startswith(('http:', 'https:', '#', 'mailto:')):
                continue
            path = link.split('#', 1)[0].split('?', 1)[0]
            assert (page.parent / path).exists(), (filename, link)
            link_count += 1

    inputs = ['breadboard/system-wiring.json', 'breadboard/system-wiring.csv',
              'breadboard/exact-wire-endpoints.csv', 'breadboard/probe-connections.csv',
              'docs/bench-checklist.csv', 'docs/build-guide.html', 'viewer/guide.json',
              'firmware/main/board.h', 'firmware/builds/validation.json',
              'docs/breadboard-refinements.html', 'docs/lab-quickstart.html',
              'docs/staged-build-guide.html', 'docs/physical-assembly.html',
              'docs/firmware-build-guide.html', 'docs/laptop-setup.html', 'docs/download-checks.html',
              'host/check_package.py', 'host/run_tests.py', 'breadboard/recording-example.json',
              'breadboard/recording-example.afolog', 'design/validate_breadboard_guidance.py']
    result = {'scope': 'AD7606 fixed-two ICM breadboard handoff', 'status': 'PASS',
              'wire_table_rows': len(wires), 'firmware_pin_comparisons': len(pins),
              'probe_contacts_verified': len(probes), 'compiled_profiles_hash_verified': len(profiles),
              'unmeasured_checklist_rows': len(checks), 'rendered_local_links_verified': link_count,
              'physical_measurements_completed': 0, 'lab_binaries_executed': False,
              'source_sha256': {name: sha256(VARIANT / name) for name in inputs},
              'note': 'Static instruction/pin/hash checks; not electrical measurements or fresh firmware execution.'}
    (VARIANT / 'breadboard/guidance-validation.json').write_text(json.dumps(result, indent=2) + '\n')
    return result


if __name__ == '__main__':
    print(json.dumps(validate(), indent=2))

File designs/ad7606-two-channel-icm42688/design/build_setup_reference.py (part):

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    'diagnostic-imu-bench-two': ('any', 'DevKit + both carriers only; 60 s PASS/FAIL verdicts'),
    'breadboard-sd-only-2ch': ('7', 'Full breadboard, SD recording, Wi-Fi off'),
    'breadboard-record-2ch': ('8–10', 'Full breadboard, SD + best-effort Wi-Fi preview'),
    'record-2ch': ('PCB', 'Compact PCB only (SD CMD on GPIO38)'),
}
PROFILE_ORDER = list(PROFILE_USE)

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        'TPS63070 buck-boost makes 3V3D (nominal 3.328 V) for the ESP32, IMUs, SD and AD7606 VDRIVE.',
        'TPS7A2030 LDO makes 3V0A for the MyoWare sensors and buffers; the buffered midpoint is 1.5 V.',
        'TPS60150 charge pump makes 5V_ADC (AVCC, 4.75–5.25 V) from 3V3D.',
        'USB VBUS is sense-only (2N7002, active-low GPIO21). Recording is refused while USB is attached.',
    ])
    story += [Paragraph('Supply-ramp fix (PCB, 12 October 2026)', ST['h2']),
              p('Because AVCC is generated from 3V3D, VDRIVE rises before AVCC, which conflicts with the AD7606 '
                'absolute maximum VDRIVE ≤ AVCC + 0.3 V and with ADI AN-1091. The PCB now holds the converter in full '
                'shutdown until both rails are up:')]
    story += bullets([
        'AD7606 STBY (pin 7) runs on net ADC_STBY to GPIO14, with R70 (100 kΩ) pulling it low; RANGE stays low.',
        'D30 (BAT760 Schottky) from 3V3D to 5V_ADC limits VDRIVE − AVCC while the charge pump starts.',
        'Firmware (PCB builds, from 1.11) releases STBY once per boot, waits the 30 ms wake-up time, then resets the ADC.',
        'KiCad DRC 0 violations / 0 unconnected, ERC 0. Breadboard builds are unchanged: the module straps STBY.',
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
    # 5. GPIO
    story += [Paragraph('5. ESP32-S3 pin map', ST['h1']),
              p('From `design/gpio-map.json` (compact PCB). The only breadboard difference is SD CMD: **GPIO47 on the '
                'DevKit breadboard, GPIO38 on the PCB**, because the DevKit drives an RGB LED on GPIO38. Flash the '
                'matching build.')]
    gp = sorted(data['gpio'].items(), key=lambda kv: int(kv[0]))
    half = (len(gp) + 1) // 2
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        a = gp[i]; b = gp[i + half] if i + half < len(gp) else ('', '')
        rows.append([a[0], a[1], b[0], b[1]])
    story += table(rows, [50, 199, 50, 200], mono_cols=(1, 3))
    story += [p('AD7606 CVA and CVB share GPIO11 (CONVST). The net named ADC_DRDY carries BUSY: the AD7606 has no '
                'separate data-ready output. SPI2 runs at 8 MHz, mode 2 (idle high, falling-edge sample). The IMUs '
                'share SPI3 on GPIO4/5/6 with separate chip selects (foot GPIO7, shank GPIO15) and INT1 lines '
                '(foot GPIO16, shank GPIO17). Full contact-level tables: `docs/build-guide.html`.')]

    # 6. IMU
    story += [Paragraph('6. Motion sensors and timing', ST['h1'])]
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        ['1.12', 'The Wi-Fi live task announces a new session (metadata packet) before that session\'s first data '
                 'packet. On 1.11 a record dequeued just after the metadata check could go first, and the laptop '
                 'dropped it as an unknown session. Found by the Wokwi IMU missing-interrupt case.'],
        ['1.11', 'PCB builds release AD7606 STBY on GPIO14, wait 30 ms, then reset (ADI AN-1091).'],
        ['1.10', 'Official ICM-42688-P datasheet cross-check; clock gates widened to ±2 %; `within_datasheet_tolerance`.'],
        ['1.9', 'IMU-only bench diagnostics with PASS/FAIL verdicts; register-level ICM model.'],
        ['1.8', 'ICM FIFO ticks converted as 32/30 µs instead of 1 µs.'],
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
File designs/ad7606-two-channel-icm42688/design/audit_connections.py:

#!/usr/bin/env python3
"""Fresh KiCad checks and direct PCB-pad comparison (requires KiCad's pcbnew Python)."""
import json,os,re,subprocess,xml.etree.ElementTree as ET
from pathlib import Path
import pcbnew
P=Path(__file__).resolve().parents[1];O=P/'docs/refinement-checks';O.mkdir(exist_ok=True)
K=os.environ.get('KICAD_CLI','/Applications/KiCad/KiCad.app/Contents/MacOS/kicad-cli')
result={'hardware_measured':False,'checks':{},'errors':[]}
for kind,cmd,ext in [('erc',['sch','erc'],'kicad_sch'),('drc',['pcb','drc'],'kicad_pcb')]:
 r=subprocess.run([K,*cmd,'--format','json','--output',str(O/(kind+'.json')),str(P/'hardware/main'/('afo_revb_main.'+ext))],capture_output=True,text=True)
 (O/(kind+'.log')).write_text(r.stdout+r.stderr);r.check_returncode()
 d=json.loads((O/(kind+'.json')).read_text());bad=d.get('violations',[])+d.get('unconnected_items',[])+[v for s in d.get('sheets',[]) for v in s.get('violations',[])]
 result['checks'][kind]={'violations':len(bad)}
 if bad:result['errors'].append([kind,bad])
subprocess.run([K,'sch','export','netlist','--format','kicadxml','--output',str(O/'netlist.xml'),str(P/'hardware/main/afo_revb_main.kicad_sch')],check=True,capture_output=True)
nets={}
for n in ET.parse(O/'netlist.xml').findall('.//nets/net'):
 for e in n.findall('node'):nets[e.get('ref'),e.get('pin')]=n.get('name').lstrip('/')
board=pcbnew.LoadBoard(str(P/'hardware/main/afo_revb_main.kicad_pcb'))
pads={}
for fp in board.GetFootprints():
 for pad in fp.Pads():pads.setdefault((fp.GetReference(),pad.GetNumber()),set()).add(pad.GetNetname().lstrip('/'))
spec=json.loads((P/'design/circuit-spec.json').read_text());count=0
for part in spec['parts']:
 for pin,net in part['pins'].items():
  if net is None:continue
  count+=1;k=(part['ref'],pin)
  if nets.get(k)!=net:result['errors'].append(['schematic',*k,net,nets.get(k)])
  if pads.get(k)!={net}:result['errors'].append(['actual PCB pad',*k,net,sorted(pads.get(k,[]))])
result['checks']['direct_schematic_and_pcb_pins']=count
# Independently transcribed ESP32-S3-WROOM-1 pad/GPIO map; compiler handles profile #if.
module={4:4,5:5,6:6,7:7,8:15,9:16,10:17,11:18,12:8,17:9,18:10,19:11,20:12,21:13,22:14,23:21,31:38,32:39,33:40,34:41,35:42,38:2,39:1}
expected={'ADC_CS':10,'ADC_CONVST':11,'ADC_RESET':9,'ADC_DRDY':8,'ADC_SCK':12,'ADC_MISO':13,'IMU_MOSI':4,'IMU_MISO':5,'IMU_SCK':6,'FOOT_CS':7,'SHANK_CS':15,'FOOT_INT':16,'SHANK_INT':17,'SD_CLK':39,'SD_D0':40,'USB_PRESENT_PIN':21,'BUTTON_PIN':18,'LED_RECORD':41,'LED_ERROR':42,'LED_BATTERY':2,'BATTERY_PIN':1}
alias={'SD_CLK':'SD_CLK_MCU','USB_PRESENT_PIN':'USB_PRESENT_N','BUTTON_PIN':'BUTTON','LED_RECORD':'LED_REC','LED_ERROR':'LED_ERR','LED_BATTERY':'LED_LOW','BATTERY_PIN':'BAT_SENSE'}
for profile in ['pcb','breadboard']:
 flags=['-DAFO_AD7606=1','-DEMG_CHANNEL_COUNT=2']+(['-DAFO_BREADBOARD=1'] if profile=='breadboard' else [])
 r=subprocess.run(['cc','-E','-dM','-x','c',*flags,str(P/'firmware/main/board.h')],capture_output=True,text=True);r.check_returncode()
 macros=dict(re.findall(r'^#define\s+(\w+)\s+(\d+)\b',r.stdout,re.M))
 values=dict(expected,SD_CMD=47 if profile=='breadboard' else 38)
 # AD7606 STBY is driven only on the PCB (AN-1091 sequence); the breadboard module keeps its own tie.
 if profile=='pcb':values['ADC_STBY']=14
 elif 'ADC_STBY' in macros and macros['ADC_STBY']!='-1':result['errors'].append(['firmware GPIO','breadboard','ADC_STBY',macros['ADC_STBY'],-1])
 for name,gpio in values.items():
  if int(macros.get(name,-1))!=gpio:result['errors'].append(['firmware GPIO',profile,name,macros.get(name),gpio])
  if profile=='pcb':
   pad=next(str(p) for p,g in module.items() if g==gpio)
   if nets.get(('U1',pad))!=alias.get(name,name):result['errors'].append(['GPIO to module',name,pad])
 result['checks'][profile+'_firmware_gpio_count']=len(values)
result['status']='FAIL' if result['errors'] else 'PASS'
(O/'connectivity.json').write_text(json.dumps(result,indent=2)+'\n');print(json.dumps(result,indent=2))
raise SystemExit(bool(result['errors']))
